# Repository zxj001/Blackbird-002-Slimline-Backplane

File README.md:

# HP BlackBird 002 Slimline SATA Back Plane PCB

**Current Working Version: 0.4**

**Latest Stable Version: 0.3**

**Latest Physical Version: 0.2**

### To Do List
* Get SMD resistor specs and components
* Get SMD LED specs and components
* Reconfigure top LED section to account for SMD LED

### Wish List
* Research button for SATA
* Find a suitable button component

### Components

| Part Type | Part Number |
|-----------|-------------|
| SATA | 678007005 |
| 8981 Molex | 0015244745 |
| Slimline SATA | 1735539 |

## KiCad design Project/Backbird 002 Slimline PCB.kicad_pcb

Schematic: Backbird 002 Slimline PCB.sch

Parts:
D1: LED; LED_D1.8mm_W3.3mm_H2.4mm
Molex_4pin1: Conn_01x04; MOLEX_8981_0015244745
R1: R 3k; Resistor_SMD+THTuniversal_2512_RM10_HandSoldering
R2: R 1k; Resistor_SMD+THTuniversal_2512_RM10_HandSoldering
Sata_Data1: Conn_01x07; SATA_DATA_678007005_CustomPad
Sata_Slimline_Recpt1: Conn_01x13; SATA_SLIMLINE_RECPT_1735539-2
Screw_Hole_B1: Conn_01x01; Blackbird002_Slimline_PCB_Screw
Screw_Hole_T1: Conn_01x01; Blackbird002_Slimline_PCB_Screw_Long

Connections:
+5V: Molex_4pin1.4, R2.2, Sata_Slimline_Recpt1.9, Sata_Slimline_Recpt1.10
A+: Sata_Data1.2, Sata_Slimline_Recpt1.2
A-: Sata_Data1.3, Sata_Slimline_Recpt1.3
B+: Sata_Data1.6, Sata_Slimline_Recpt1.6
B-: Sata_Data1.5, Sata_Slimline_Recpt1.5
GND: D1.1 (K), Molex_4pin1.2, Molex_4pin1.3, R1.1, Sata_Data1.1, Sata_Data1.4, Sata_Data1.7, Sata_Slimline_Recpt1.1, Sata_Slimline_Recpt1.4, Sata_Slimline_Recpt1.7, Sata_Slimline_Recpt1.12, Sata_Slimline_Recpt1.13
unnamed: D1.2 (A), R1.2, R2.1

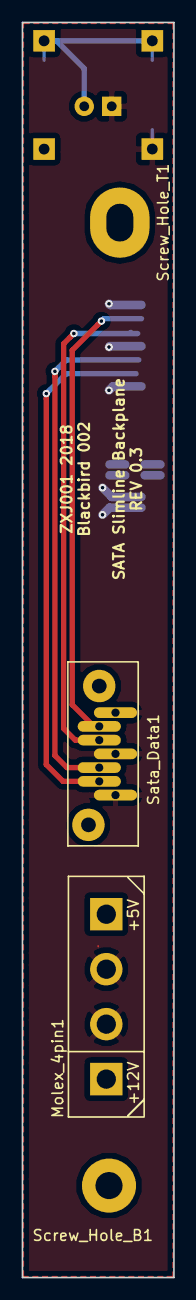
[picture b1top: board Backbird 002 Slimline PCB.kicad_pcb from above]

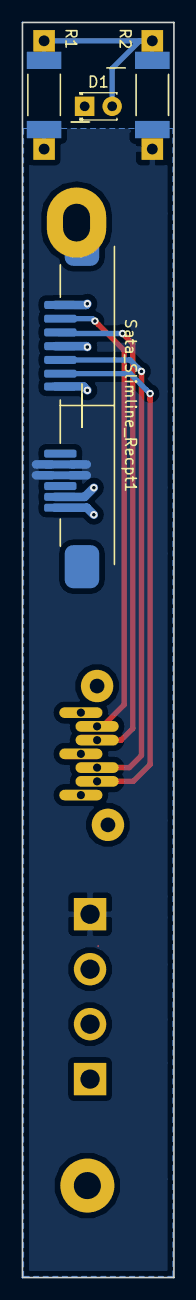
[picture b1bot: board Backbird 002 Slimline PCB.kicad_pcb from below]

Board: 2 copper layers, 14.0 x 116.0 mm, 8 parts (4 on the bottom side), 7 nets.

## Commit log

2018-06-01 Initial commit for a Sata Slimline backpane PCB
2018-06-06 moved files to new folder for organization
2018-06-07 added a spreadsheet to keep track of components
2018-06-07 Removed unused extra libraries folder from project preferences
2018-06-07 Upgraded project to KiCad 5 RC2 nightly build (kicad-20180606-033155.9552e02-c4osx)
2018-06-07 Fixed pinout of Sata data ports to be 7-pin instead of 6
2018-06-07 Annotated schematic
2018-06-08 Added Footprints for Molex Power, Sata Data, and Sata Slimline connectors.
2018-06-08 Added holes for blocking off the LED. Also added an additional connector for power
2018-06-08 First pass at building the PCB using footprints. Fixed Sata Slimeline Recpt footprint by numbering the pins from 1-13 and adding mechanical pads. Made molex 8981 footprint cleaner by adding the notch.
2018-06-08 Updated PSB layout. (might remove extra power and Sata locations) Added custom footprints for screws and for a generic 8981 power pinout.
2018-06-09 Removed extra connectors from PCB
2018-06-10 Fixed Sata Slimline footprint to have pads instead of holes. Moved Sata receptacle to the back side of the PCB
2018-06-10 Added elongated screw hole
2018-06-10 Moved LED and resistors to the back side of the PCB
2018-06-12 Moved silk screen of resistors and LED power holes to be on the PCB.
2018-06-14 Moved top drill hole and Sata Recpt into the correct positions. Edited the pads on the Sata Recpt footprint to be more accurate. Still need to add traces
2018-06-14 Improved trace widths and zone fills
2018-06-17 Connected top components
2018-06-22 Edited receptacle so that the origin of the pads are lower instead of in the center
2018-06-22 remove extra 2 holes for the LED section
2018-06-22 Updated silkscreen to include description
2018-06-23 Fix SATA padding by having the drill in the center of the pad to meet OSHPark's expectations.
2018-07-10 Moved bottom screw hole into correct position
2018-07-10 Changed hole size to 2.5mm from 3mm and total diameter from 6 to 5
2018-07-10 Updated screw hole on the PCB to the new footprint.
2018-07-11 Moved top screw hole closer to edge
2018-07-11 Shrank top (long) screw hole by 0.5mm on each dimension
2018-07-11 Moved 4pin power connector down ~3mm
2018-07-11 Traces are now at least 0.5mm wide. Added more traces for the +5V SATA power connector
2018-07-11 Moved data traces more inward so the power plane isn't cut off
2018-07-11 Added rev 0.3 text
2018-07-11 Refilled power planes. Adjusted traces for SATA connection. Added README file with component part numbers
2018-07-14 Updated README
    Added to-do lists and version numbers.
